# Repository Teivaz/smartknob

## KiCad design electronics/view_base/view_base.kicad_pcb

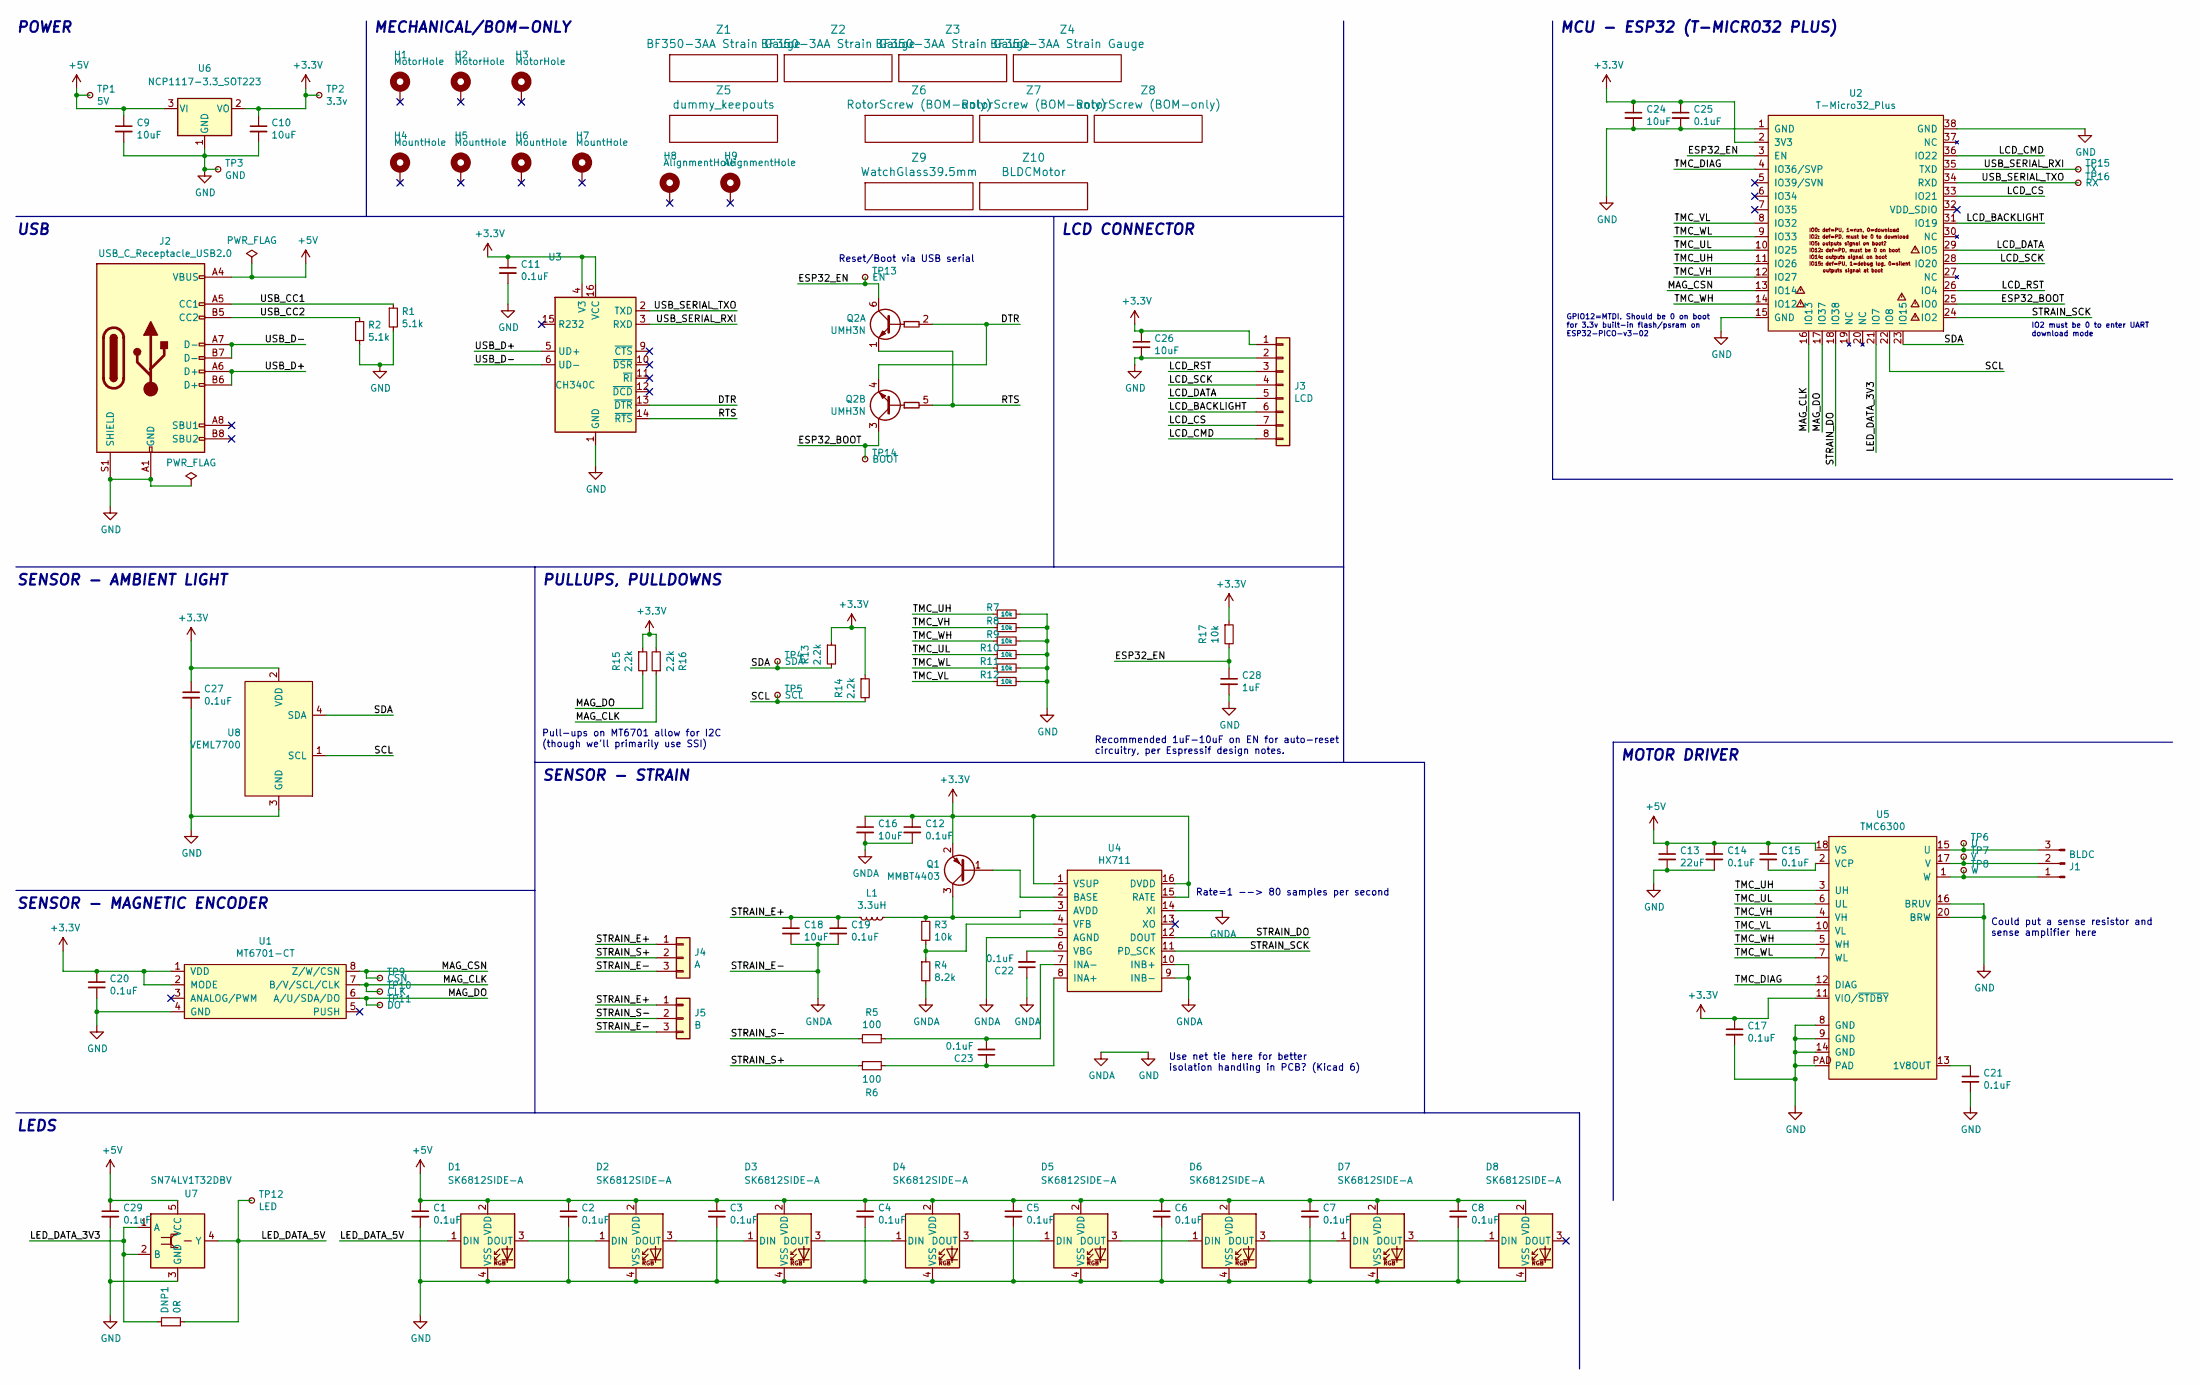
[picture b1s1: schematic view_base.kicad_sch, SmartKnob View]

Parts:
C1, C2, C3, C4, C5, C6, C7, C8, C11, C12, C14, C15, C17, C19, C20, C21, C22, C23, C25, C27, C29: 0.1uF; C_0603_1608Metric; LCSC C1591
C9, C10, C16, C18, C24, C26: 10uF; C_0805_2012Metric; LCSC C2922480
C13: 22uF; C_0805_2012Metric; LCSC C98190
C28: 1uF; C_0603_1608Metric; Mouser 187-CL10A105KA8NNNC
D1, D2, D3, D4, D5, D6, D7, D8: SK6812SIDE-A; SK6812-SIDE-A; Digikey 1528-4691-ND
DNP1: 0R; R_0603_1608Metric; LCSC C98220
H1, H2, H3: MotorHole; MountingHole_M1.6
H4, H5, H6, H7: MountHole; MountingHole_2.2mm_M2_ISO7380_Pad_NonVirtual
H8, H9: AlignmentHole; MountingHole_2.2mm_M2_ISO7380_Pad_NonVirtual
J1: BLDC; Molex_Pico-Lock_504050-0591_1x05-1MP_P1.50mm_Horizontal; LCSC C293630
J2: USB_C_Receptacle_USB2.0; USB4510_NoPaste; LCSC C428463
J3: LCD; SolderPads_2mm_8
J4: A; SolderPads_2mm_3_STRAIN
J5: B; SolderPads_2mm_3_STRAIN
L1: 3.3uH; L_0805_2012Metric; LCSC C307744
Q1: MMBT4403; SOT-23; LCSC C78864
Q2: UMH3N; SOT-363_SC-70-6; LCSC C62892
R1, R2: 5.1k; R_0603_1608Metric; LCSC C105580
R3, R7, R8, R9, R10, R11, R12, R17: 10k; R_0603_1608Metric; LCSC C98220
R4: 8.2k; R_0603_1608Metric; LCSC C114637
R5, R6: 100; R_0603_1608Metric; LCSC C319953
R13, R14, R15, R16: 2.2k; R_0603_1608Metric; LCSC C4190
TP1: 5V; TestPoint_Pad_D2.0mm_ValueSilk
TP2: 3.3v; TestPoint_Pad_D2.0mm_ValueSilk
TP3: GND; TestPoint_Pad_D2.0mm_ValueSilk
TP4: SDA; TestPoint_Pad_D2.0mm_ValueSilk
TP5: SCL; TestPoint_Pad_D2.0mm_ValueSilk
TP6: U; TestPoint_Pad_D2.0mm_ValueSilk
TP7: V; TestPoint_Pad_D2.0mm_ValueSilk
TP8: W; TestPoint_Pad_D2.0mm_ValueSilk
TP9: CSN; TestPoint_Pad_D2.0mm_ValueSilk
TP10: CLK; TestPoint_Pad_D2.0mm_ValueSilk
TP11: DO; TestPoint_Pad_D2.0mm_ValueSilk
TP12: LED; TestPoint_Pad_D2.0mm_ValueSilk
TP13: EN; TestPoint_Pad_D2.0mm_ValueSilk
TP14: BOOT; TestPoint_Pad_D2.0mm_ValueSilk
TP15: TX; TestPoint_Pad_D2.0mm_ValueSilk
TP16: RX; TestPoint_Pad_D2.0mm_ValueSilk
U1: MT6701-CT; SOIC-8_3.9x4.9mm_P1.27mm; LCSC C2856764
U2: T-Micro32_Plus; T-Micro32; Digikey N/A
U3: CH340C; SOIC-16_3.9x9.9mm_P1.27mm; LCSC C84681
U4: HX711; SOIC-16_3.9x9.9mm_P1.27mm; LCSC C43656
U5: TMC6300; QFN-20-1EP_3x3mm_P0.4mm_EP1.65x1.65mm_ThermalVias_LargerVia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; Digikey TMC6300-LA-T
U6: NCP1117-3.3_SOT223; SOT-223-3_TabPin2
U7: SN74LV1T32DBV; SOT-23-5
U8: VEML7700; VEML7700-TOP; Digikey VEML7700-TT
Z1, Z2, Z3, Z4: BF350-3AA Strain Gauge; BF350-3AA; Digikey N/A
Z5: dummy_keepouts; ViewKeepouts3d
Z6, Z7, Z8: RotorScrew (BOM-only); bom_only_no_pin
Z9: WatchGlass39.5mm; bom_only_no_pin
Z10: BLDCMotor; bom_only_no_pin

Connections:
+3.3V: C10.1, C11.1, C12.1, C16.1, C17.1, C20.1, C24.1, C25.1, C26.1, C27.1, J3.1, Q1.2 (E), R13.1, R14.1, R15.1, R16.2, R17.1, TP2.1, U1.1 (VDD), U1.2 (MODE), U2.2 (3V3), U3.4 (V3), U3.16 (VCC), U4.1 (VSUP), U4.15 (RATE), U4.16 (DVDD), U5.11 (VIO/~STDBY), U6.2 (VO), U8.2 (VDD)
+5V: C1.1, C2.1, C3.1, C4.1, C5.1, C6.1, C7.1, C8.1, C9.1, C13.1, C14.1, C15.1, C29.1, D1.2 (VDD), D2.2 (VDD), D3.2 (VDD), D4.2 (VDD), D5.2 (VDD), D6.2 (VDD), D7.2 (VDD), D8.2 (VDD), J2.A4 (VBUS), J2.A9 (VBUS), J2.B4 (VBUS), J2.B9 (VBUS), TP1.1, U5.18 (VS), U6.3 (VI), U7.5 (VCC)
/DTR: Q2.2 (B1), Q2.4 (E2), U3.13 (~DTR)
/ESP32_BOOT: Q2.3 (C2), TP14.1, U2.25 (IO0)
/ESP32_EN: C28.1, Q2.6 (C1), R17.2, TP13.1, U2.3 (EN)
/LCD_BACKLIGHT: J3.6, U2.31 (IO19)
/LCD_CMD: J3.8, U2.36 (IO22)
/LCD_CS: J3.7, U2.33 (IO21)
/LCD_DATA: J3.5, U2.29 (IO5)
/LCD_RST: J3.3, U2.26 (IO4)
/LCD_SCK: J3.4, U2.28 (IO20)
/LED_DATA_3V3: DNP1.1, U2.21 (IO7), U7.1 (A), U7.2 (B)
/LED_DATA_5V: D1.1 (DIN), DNP1.2, TP12.1, U7.4 (Y)
/MAG_CLK: R16.1, TP10.1, U1.7 (B/V/SCL/CLK), U2.16 (IO13)
/MAG_CSN: TP9.1, U1.8 (Z/W/CSN), U2.13 (IO14)
/MAG_DO: R15.2, TP11.1, U1.6 (A/U/SDA/DO), U2.17 (IO37)
/RTS: Q2.1 (E1), Q2.5 (B2), U3.14 (~RTS)
/SCL: R14.2, TP5.1, U2.22 (IO8), U8.1 (SCL)
/SDA: R13.2, TP4.1, U2.23 (IO15), U8.4 (SDA)
/STRAIN_DO: U2.18 (IO38), U4.12 (DOUT)
/STRAIN_E+: C18.1, C19.1, J4.1, J5.1, L1.2
/STRAIN_S+: J4.2, R6.1
/STRAIN_S-: J5.2, R5.2
/STRAIN_SCK: U2.24 (IO2), U4.11 (PD_SCK)
/TMC_DIAG: U2.4 (IO36/SVP), U5.12 (DIAG)
/TMC_UH: R7.1, U2.11 (IO26), U5.3 (UH)
/TMC_UL: R10.1, U2.10 (IO25), U5.6 (UL)
/TMC_VH: R8.1, U2.12 (IO27), U5.4 (VH)
/TMC_VL: R12.1, U2.8 (IO32), U5.10 (VL)
/TMC_WH: R9.1, U2.14 (IO12), U5.5 (WH)
/TMC_WL: R11.1, U2.9 (IO33), U5.7 (WL)
/USB_CC1: J2.A5 (CC1), R1.1
/USB_CC2: J2.B5 (CC2), R2.1
/USB_D+: J2.A6 (D+), J2.B6 (D+), U3.5 (UD+)
/USB_D-: J2.A7 (D-), J2.B7 (D-), U3.6 (UD-)
/USB_SERIAL_RXI: TP15.1, U2.35 (TXD), U3.3 (RXD)
/USB_SERIAL_TXO: TP16.1, U2.34 (RXD), U3.2 (TXD)
GND: C1.2, C2.2, C3.2, C4.2, C5.2, C6.2, C7.2, C8.2, C9.2, C10.2, C11.2, C12.2, C13.2, C14.2, C16.2, C17.2, C18.2, C19.2, C20.2, C21.2, C22.1, C24.2, C25.2, C26.2, C27.2, C28.2, C29.2, D1.4 (VSS), D2.4 (VSS), D3.4 (VSS), D4.4 (VSS), D5.4 (VSS), D6.4 (VSS), D7.4 (VSS), D8.4 (VSS), J2.A1 (GND), J2.A12 (GND), J2.B1 (GND), J2.B12 (GND), J2.S1 (SHIELD), J3.2, J4.3, J5.3, R1.2, R2.2, R4.2, R7.2, R8.2, R9.2, R10.2, R11.2, R12.2, TP3.1, U1.4 (GND), U2.1 (GND), U2.15 (GND), U2.38 (GND), U3.1 (GND), U4.5 (AGND), U4.9 (INB-), U4.10 (INB+), U4.14 (XI), U5.8 (GND), U5.9 (GND), U5.14 (GND), U5.16 (BRUV), U5.20 (BRW), U5.PAD, U6.1 (GND), U7.3 (GND), U8.3 (GND)
unnamed: C15.2, U5.2 (VCP)
unnamed: C21.1, U5.13 (1V8OUT)
unnamed: C22.2, U4.6 (VBG)
unnamed: C23.1, R6.2, U4.8 (INA+)
unnamed: C23.2, R5.1, U4.7 (INA-)
unnamed: D1.3 (DOUT), D2.1 (DIN)
unnamed: D2.3 (DOUT), D3.1 (DIN)
unnamed: D3.3 (DOUT), D4.1 (DIN)
unnamed: D4.3 (DOUT), D5.1 (DIN)
unnamed: D5.3 (DOUT), D6.1 (DIN)
unnamed: D6.3 (DOUT), D7.1 (DIN)
unnamed: D7.3 (DOUT), D8.1 (DIN)
unnamed: J1.1, TP8.1, U5.1 (W)
unnamed: J1.2, TP7.1, U5.17 (V)
unnamed: J1.3, TP6.1, U5.15 (U)
unnamed: L1.1, Q1.3 (C), R3.1, U4.3 (AVDD)
unnamed: Q1.1 (B), U4.2 (BASE)
unnamed: R3.2, R4.1, U4.4 (VFB)

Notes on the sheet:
PULLUPS, PULLDOWNS
Reset/Boot via USB serial
SENSOR - STRAIN
MCU - ESP32 (T-MICRO32 PLUS)
USB
Use net tie here for better isolation handling in PCB? (Kicad 6)
Recommended 1uF-10uF on EN for auto-reset circuitry, per Espressif design notes.
POWER
GPIO12=MTDI. Should be 0 on boot for 3.3v built-in flash/psram on ESP32-PICO-v3-02
Could put a sense resistor and sense amplifier here
LCD CONNECTOR
Rate=1 --> 80 samples per second
MECHANICAL/BOM-ONLY
MOTOR DRIVER
SENSOR - AMBIENT LIGHT
LEDS
IO2 must be 0 to enter UART download mode
SENSOR - MAGNETIC ENCODER
Pull-ups on MT6701 allow for I2C (though we'll primarily use SSI)

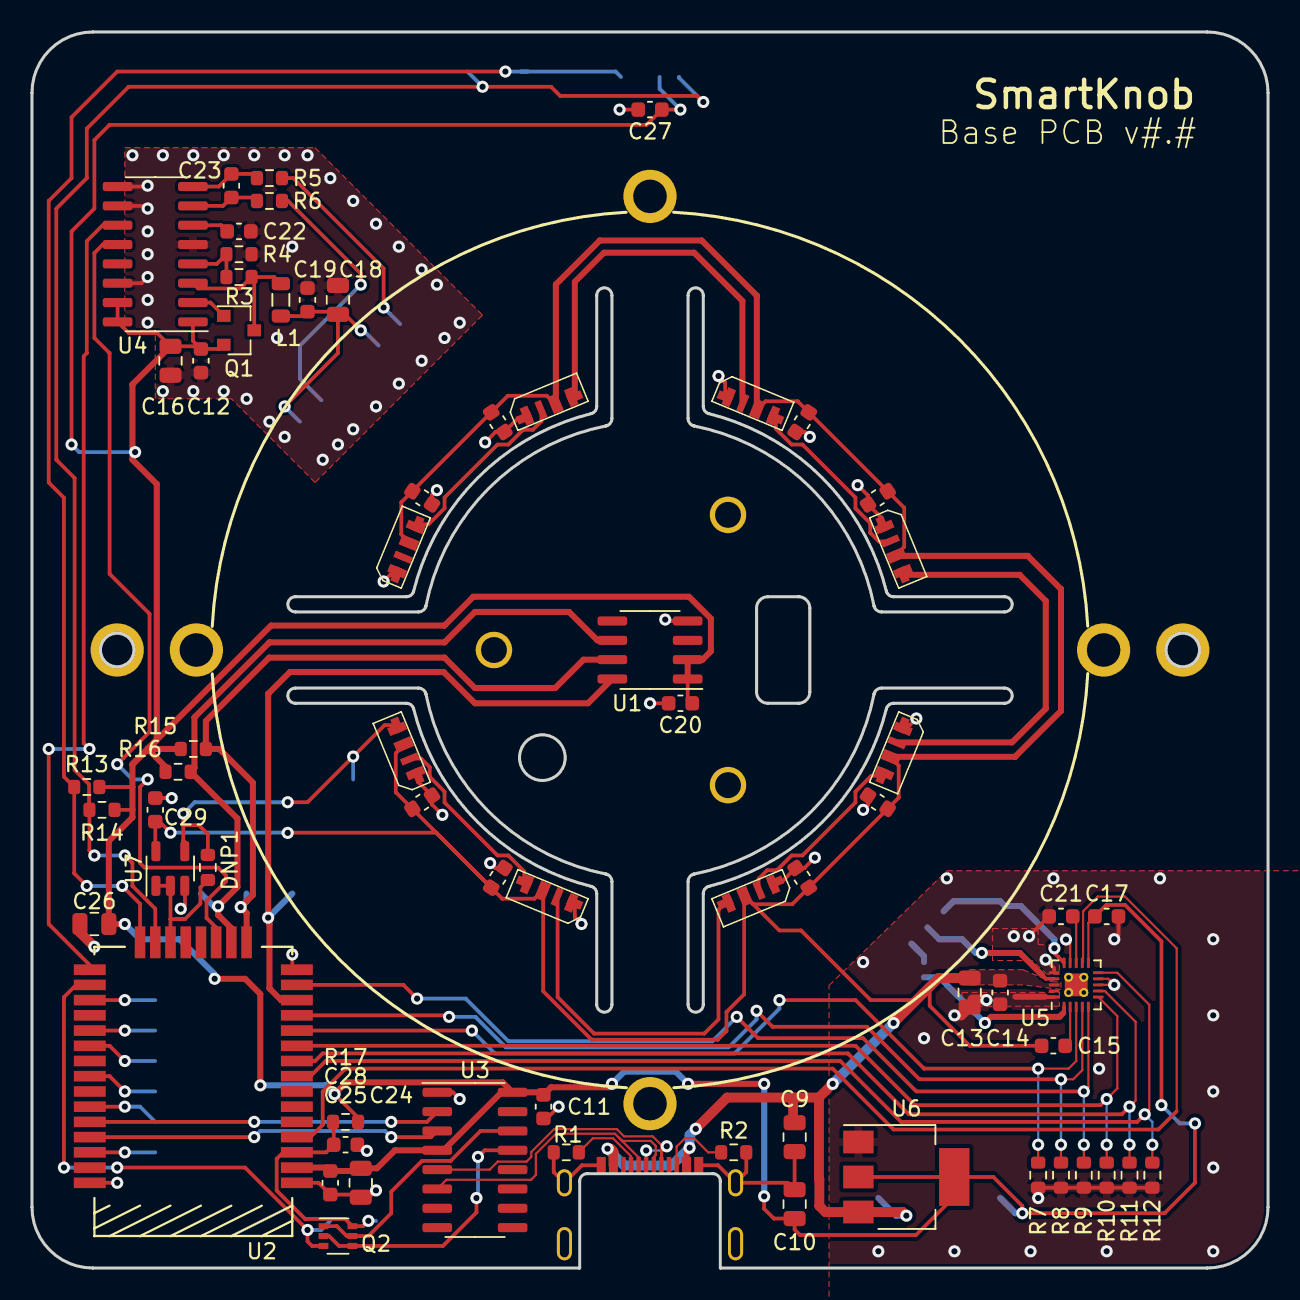
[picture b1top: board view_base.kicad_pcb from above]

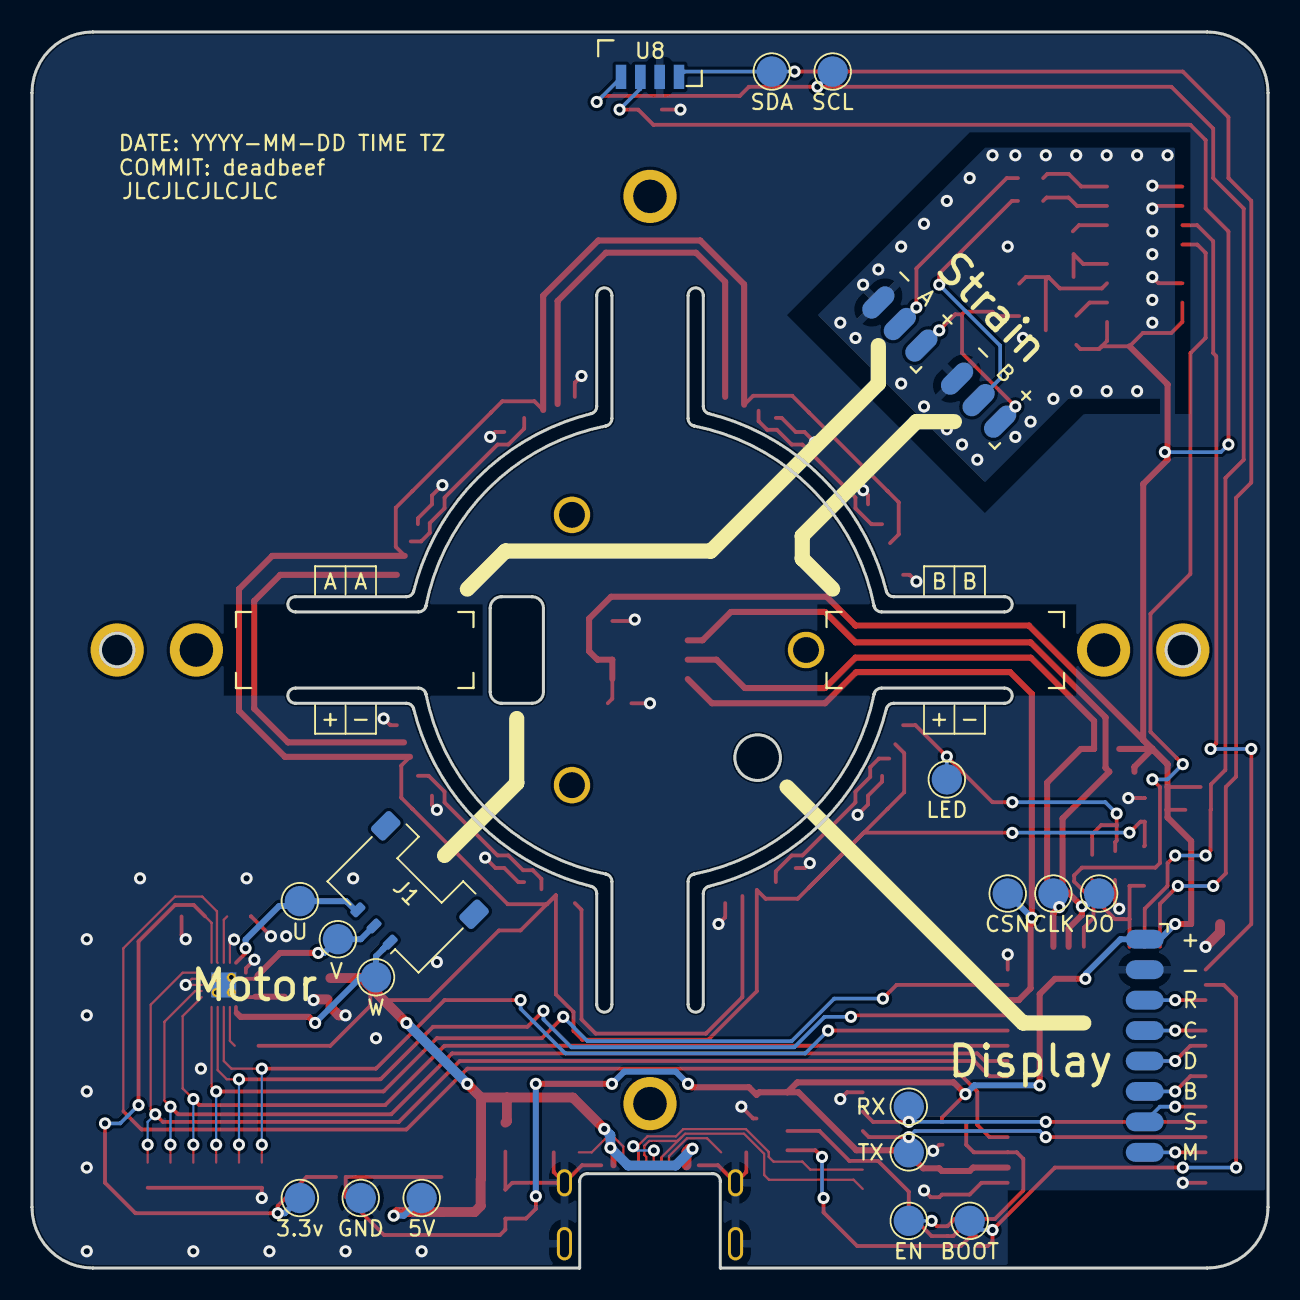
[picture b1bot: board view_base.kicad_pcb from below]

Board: 2 copper layers, 81.2 x 81.2 mm, 106 parts (25 on the bottom side), 56 nets.

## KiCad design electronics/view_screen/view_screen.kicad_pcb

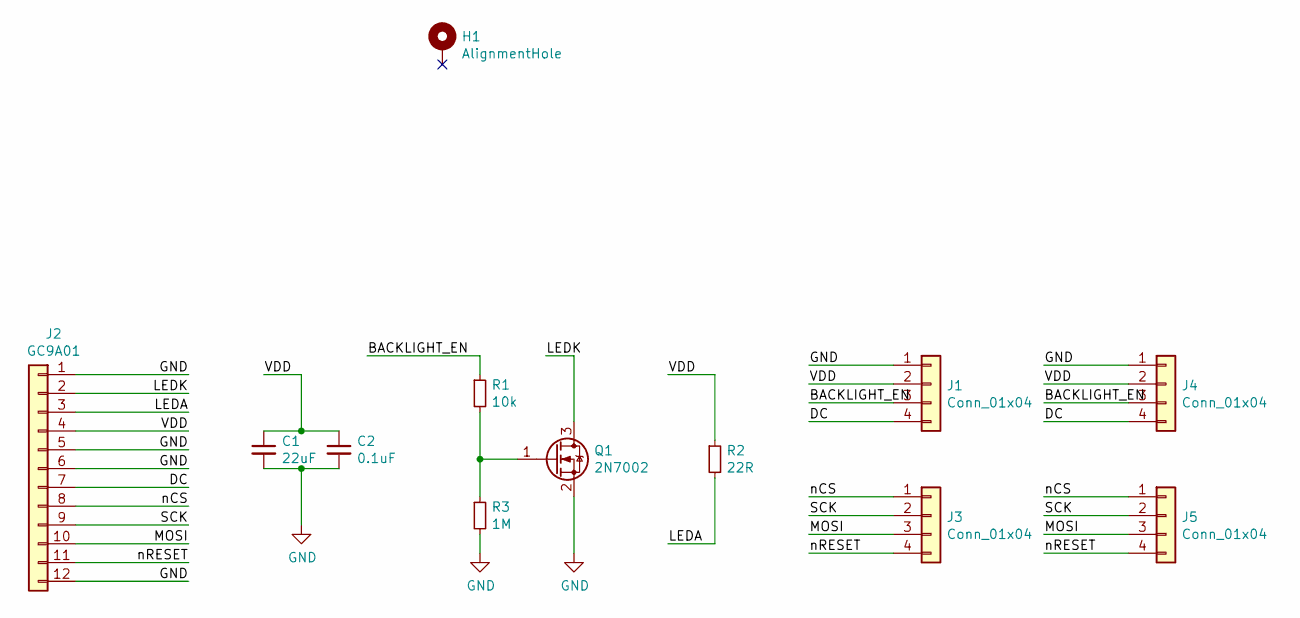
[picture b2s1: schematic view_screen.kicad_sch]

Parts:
C1: 22uF; C_0805_2012Metric; Digikey 1276-CL21A226MAYNNNECT-ND
C2: 0.1uF; C_0603_1608Metric; Digikey 1276-1935-1-ND
H1: AlignmentHole; AlignmentHole_1.6
J1, J3, J4, J5: Conn_01x04; SolderPads_2mm_4
J2: GC9A01; GC9A01Round1.28; Digikey N/A
Q1: 2N7002; SOT-23; Digikey 2N7002H6327XTSA2CT-ND
R1: 10k; R_0603_1608Metric; Digikey RMCF0603JT10K0CT-ND
R2: 22R; R_0603_1608Metric; Digikey RMCF0603JT22R0CT-ND
R3: 1M; R_0603_1608Metric; Digikey RMCF0603JT1M00CT-ND

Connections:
/BACKLIGHT_EN: J1.3, J4.3, R1.1
/DC: J1.4, J2.7, J4.4
/LEDA: J2.3, R2.2
/LEDK: J2.2, Q1.3 (D)
/MOSI: J2.10, J3.3, J5.3
/SCK: J2.9, J3.2, J5.2
/VDD: C1.1, C2.1, J1.2, J2.4, J4.2, R2.1
/nCS: J2.8, J3.1, J5.1
/nRESET: J2.11, J3.4, J5.4
GND: C1.2, C2.2, J1.1, J2.1, J2.5, J2.6, J2.12, J4.1, Q1.2 (S), R3.2
unnamed: Q1.1 (G), R1.2, R3.1

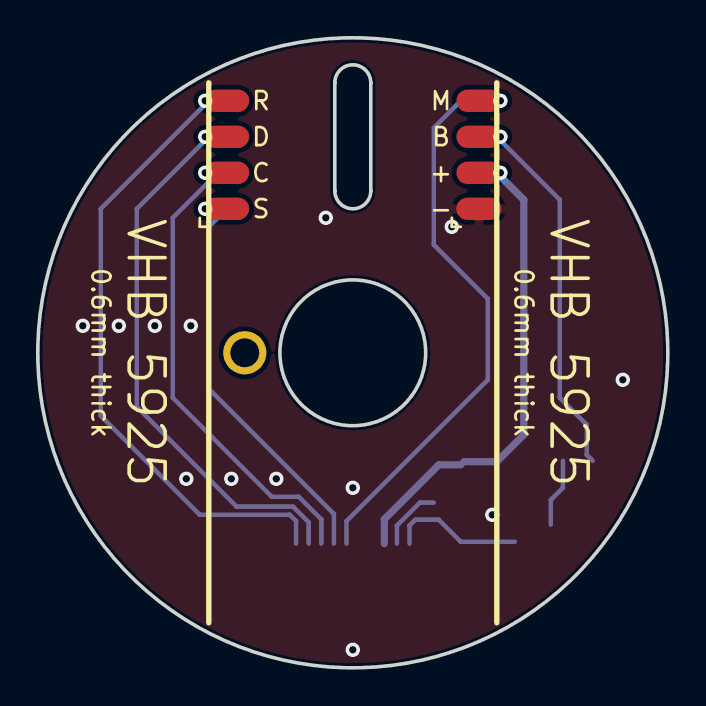
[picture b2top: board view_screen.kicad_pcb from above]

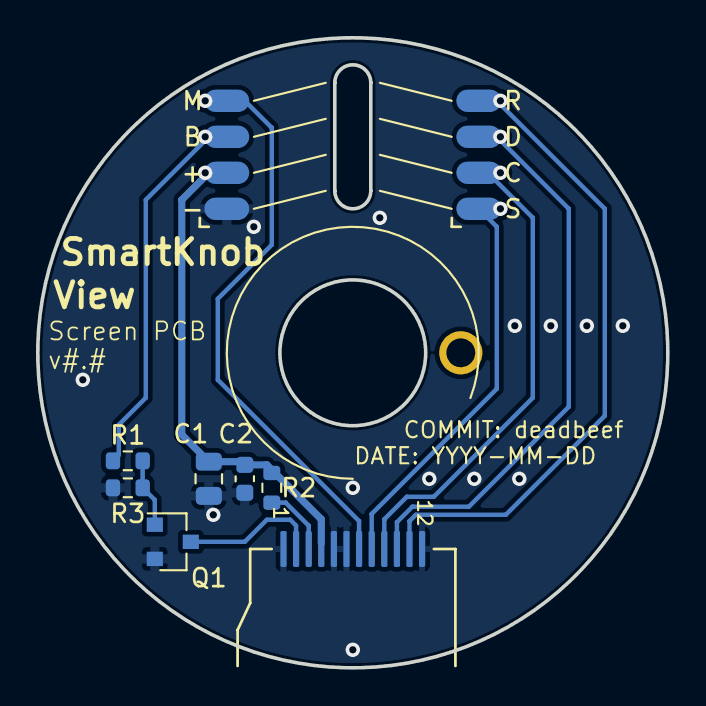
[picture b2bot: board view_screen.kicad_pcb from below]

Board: 2 copper layers, 35.0 x 35.0 mm, 12 parts (9 on the bottom side), 11 nets.

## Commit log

2022-08-08 Updated to Kicad 6 Replaced following parts: SN74LV1T34DBV -> SN74LV1T32DBVRG4 AP2114HA-3.3 -> NCP11171IST33T3G
2022-08-28 Added DNP resistor to bypass level shift
2022-08-28 Updated text
2022-08-28 Updated github hoook
2022-08-28 Bumped version of kikit
2022-08-29 Bumped version of kicad
2022-08-29 Fixed DRC violations
2022-08-29 Fixed script deprecated method error
2022-08-29 disabled rendering step in github actions
2022-08-29 Fixed artifact names
2022-08-29 Updated kibot rules
2022-08-29 Disabled DRC
2022-08-29 Added missing library
2022-08-29 Updated libraries after migration to kicad 6 Updated gitignore after migration to kicad 6
2022-08-29 disabled ERC
2022-08-29 Updated view_screen to kicad 6
2022-09-11 Replaced motor connector with molex picolock
